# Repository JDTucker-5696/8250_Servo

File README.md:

# 8250_Servo
8250 disk interface board for MPI drives

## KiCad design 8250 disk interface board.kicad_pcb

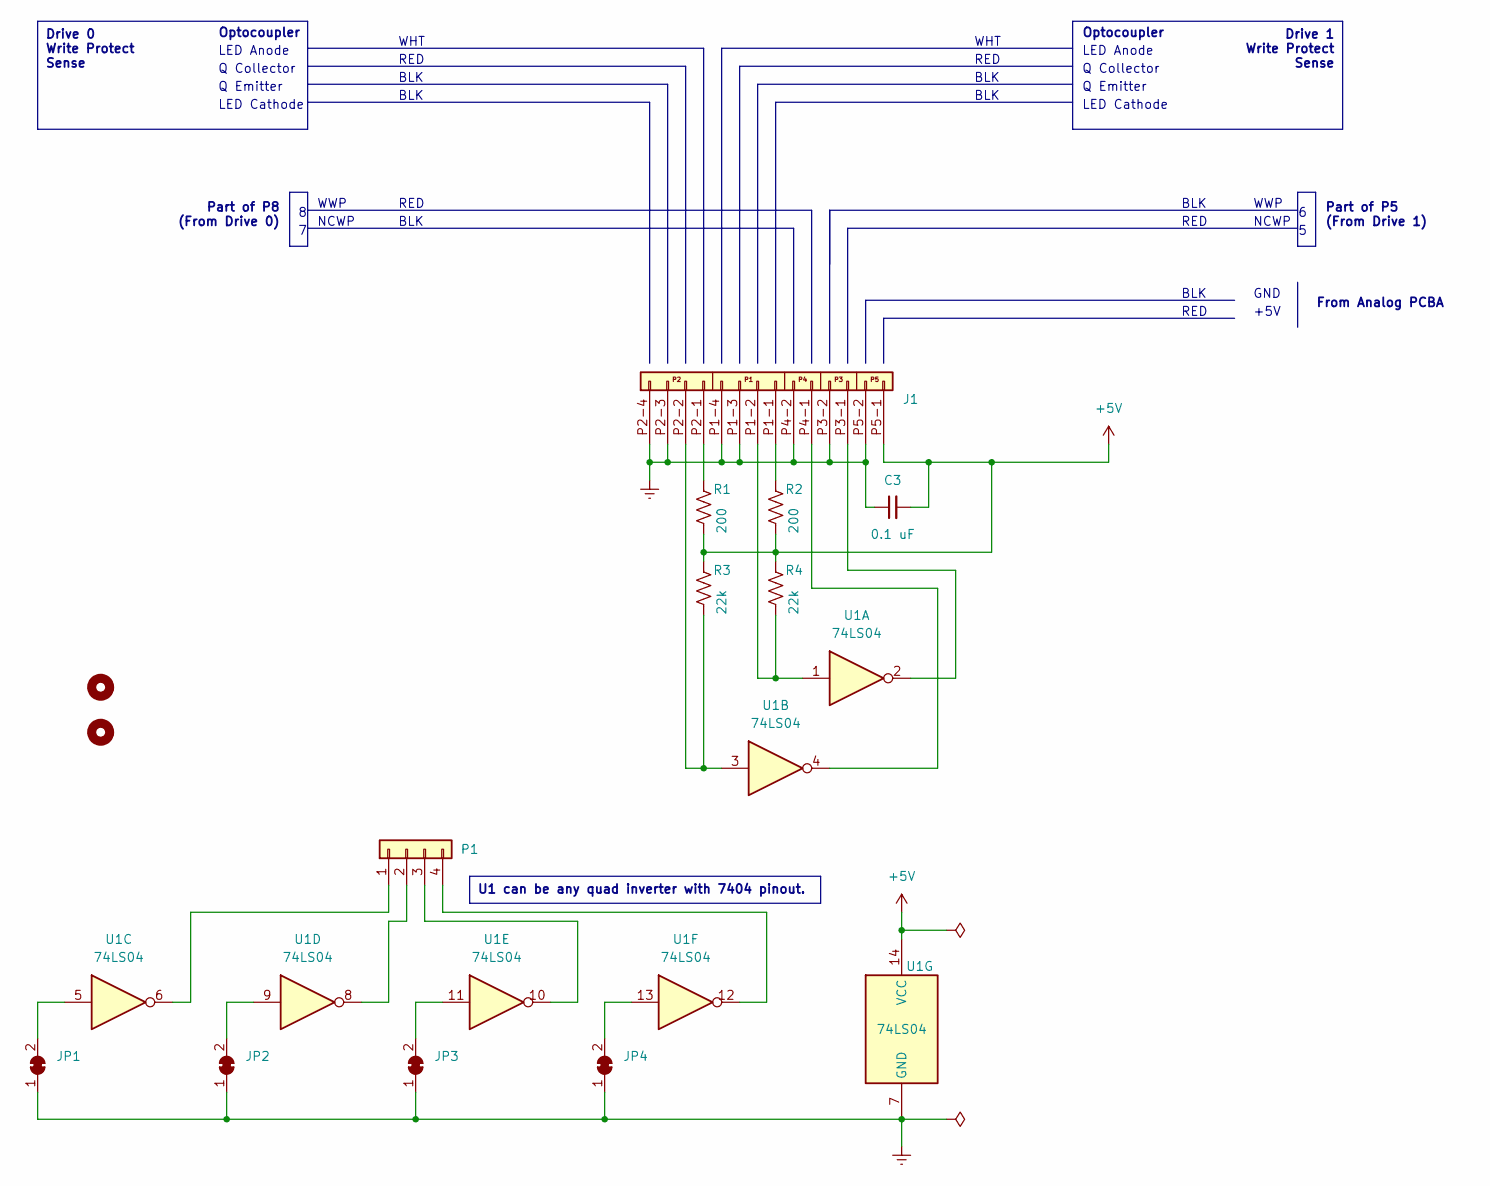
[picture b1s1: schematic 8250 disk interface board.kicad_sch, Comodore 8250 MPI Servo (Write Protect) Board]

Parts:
C3: 0.1 uF; C_Disc_D3.0mm_W1.6mm_P2.50mm
H1, H2: MountingHole; MountingHole_3.2mm_M3
J1: 01x14_Servo connector; 8250_14-pin_connector
JP1, JP2, JP3, JP4: SolderJumper_2_Bridged; SolderJumper-2_P1.3mm_Open_Pad1.0x1.5mm
P1: Conn_01x04; PinHeader_1x04_P2.54mm_Vertical
R1, R2: 200; R_Axial_DIN0204_L3.6mm_D1.6mm_P5.08mm_Horizontal
R3, R4: 22k; R_Axial_DIN0204_L3.6mm_D1.6mm_P5.08mm_Horizontal
U1: 74LS04; DIP-14_W7.62mm_Socket_LongPads

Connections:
+5V: C3.2, J1.P5-1 (Pin_01), R1.2, R2.2, R3.1, R4.1, U1.14 (VCC)
Earth: C3.1, J1.P1-3 (Pin_19), J1.P1-4 (Pin_10), J1.P2-3 (Pin_13), J1.P2-4 (Pin_14), J1.P3-2 (Pin_04), J1.P4-2 (Pin_06), J1.P5-2 (Pin_02), JP1.1 (A), JP2.1 (A), JP3.1 (A), JP4.1 (A), U1.7 (GND)
unnamed: J1.P3-1 (Pin_03), U1.2
unnamed: J1.P4-1 (Pin_05), U1.4
unnamed: J1.P1-1 (Pin_07), R2.1
unnamed: J1.P1-2 (Pin_08), R4.2, U1.1
unnamed: J1.P2-1 (Pin_11), R1.1
unnamed: J1.P2-2 (Pin_12), R3.2, U1.3
unnamed: JP1.2 (B), U1.5
unnamed: JP2.2 (B), U1.9
unnamed: JP3.2 (B), U1.11
unnamed: JP4.2 (B), U1.13
unnamed: P1.1, U1.6
unnamed: P1.2, U1.8
unnamed: P1.3, U1.10
unnamed: P1.4, U1.12

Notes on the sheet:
U1 can be any quad inverter with 7404 pinout.
Drive 1 Write Protect Sense
Drive 0 Write Protect Sense
RED
Part of P8 (From Drive 0)
BLK
Optocoupler
Q Collector
WHT
NCWP
WWP
GND
LED Cathode
+5V
Q Emitter
LED Anode
From Analog PCBA
Part of P5 (From Drive 1)

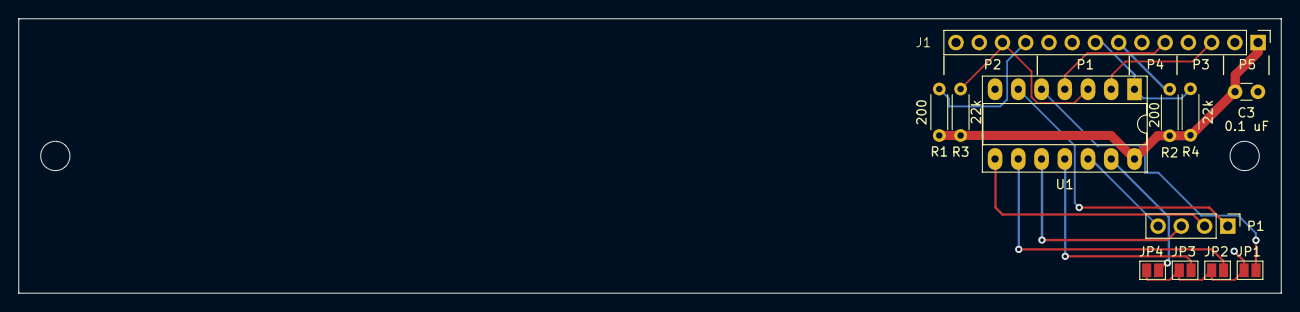
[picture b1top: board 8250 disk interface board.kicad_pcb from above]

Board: 2 copper layers, 138.0 x 30.0 mm, 14 parts (0 on the bottom side), 16 nets.

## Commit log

2023-09-27 Sent off to OshPark
2023-09-27 Set copper to edge from 0.25mm to >15mil (0.38mm).
